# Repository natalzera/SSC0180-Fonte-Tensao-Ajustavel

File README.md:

# SSC0180-Fonte-Tensao-Ajustavel

## Objetivos
Montar/esquematizar uma fonte de tensão ajustável (corrente contínua)  entre 3V a 12V com capacidade de 100mA em 12V

## Componentes
Componente     | Quantidade | Preço Total(R$)
---            | ---        | ---
Transformador 15V 500mA | 1          | 31,60
Diodos 1N4007           | 4          | 0,40
Capacitor 470uF 25V     | 1          | 0,41
Resistor 470Ω        | 1          | 0,05
Diodo Zener 13V 0,5W    | 1          | 0,08
Potenciômetro 1KΩ        | 1          | 1,99
Resistor 390Ω        | 1          | 0,05
Transistor NPN 45V 500mA | 1          | 0,20
TOTAL | -- | 34.78

* Transformador.  
O transformador escolhido é o componente responsavel por abaixar a tensão da tomada (220 V) para uma tensão mais proxima da que que será trabalhada (12-3 V). O transformador em questão leva *110V ou 220V para 15V*.  
[link para compra](https://www.baudaeletronica.com.br/transformador-trafo-500ma-15v.html)
 
* Diodos.  
Os diodos são usados para formar a ponte retificadora/ ponte de diodos. Essa ponte é responsavel por proporcionar o maior aproveitamento da energia, abastecendo o circito com a corrente em ambos os ciclos da corrente alternada. O escolhido para o projeto é o *Diodo 1N4007*.  
[link para compra](https://www.baudaeletronica.com.br/diodo-1n4007.html)

* Capacitor.  
O capacitor é responsavel por carregar o sistema quando a tensão (vinda da ponde de diodos) está em declinio, estabilizando a tensão que vai para o restante do circuito e criando o "ripple". O capacitor escolhido é um de 470uF, para criar um riplle de até 10%
[link para compra](https://www.baudaeletronica.com.br/capacitor-eletrolitico-470uf-25v.html)

* Resistores.  
O circuito implementa 2 resistores.  
O primeiro, *de 470ohms*, é responsavel por limitar a corrente passando pelo diodo Zener e pelo potenciômetro. Esse valor foi calculado para causar uma queda de tensão de até 5V quando o ripple esta no minimo (~18V).  
O segundo, *de 390ohms*, limita a tensão minima para aproximadamente 3,7V, fazendo com que o potencial de saida do potenciômetro esteja sempre entre ~12,7 ~3,7V.  
[link para compra (470ohms)](https://www.baudaeletronica.com.br/resistor-470r-5-1-4w.html)  
[link para compra (390ohms)](https://www.baudaeletronica.com.br/resistor-390r-5-1-4w.html)  

* Diodo Zener  
O diodo Zener é usado como limitador de tensão no circuito. O diodo escolhido tem tensão de regulação de 13V, ou seja, ele limita a tensão na saida dele a 13V constantes. Ele sera usado para causar uma tensão de referência para o transistor. O escolhido foi o *Diodo Zener BZX55C*.  
[link para compra](https://www.baudaeletronica.com.br/diodo-zener-bzx55c-13v-0-5w.html)

* Potenciômetro  
O potenciômetro recebe a corrente em paralelo com o diodo Zener, e por tanto tem potencial fixo em aprimadamente 13V (ocorre uma pequena queda do potencial devido as conexões do componente no resto do circuito, mas essa é negligenciavel para nossas aplicações). Assim, ele contrala a tensão mínima (~3V) e máxima (~12V) que vai para o transistor de controle.  
[link para compra](https://www.baudaeletronica.com.br/potenciometro-linear-rotativo-de-1k-1000.html)

* Transistor  
Por fim, o transistor é responsavel por amplificar a corrente que passa pela carga. Utilizando a corrente que passa pela base como referência, ele amplifica essa em 100 vezes. No pior caso (12V) ele recebe 1mA na base, e emite 100mA pelo emissor. O transistor escolhido foi o *Transistor NPN BC337*.  
[link para compra](https://www.baudaeletronica.com.br/transistor-npn-bc337.html)

[Circuito simulado no falstad](https://www.falstad.com/circuit/circuitjs.html?ctz=CQAgjCAMB0l3BWcAOaAmA7MgnGB-kA2MAFgwTRBMJCRIGZaBTAWjDACgB3K5SENMmRUwNQcMgd6JEAC8mAOyYAnNvRYyIYaBlL0KyMNkFh4aVhigDY8W3cjJNjTrJFihbgWhmV5S1WDqJBzKnqL8JKJeMhEYkjwIJD4eJHwCHvG0SeCE-ImaxlDcnmjeVKnRRaH5lTXiVmBomZE04VmauUUALlTYYg7tAgP8ECyE0IYYaNgUJJB9eI1QOqTYkIn09KQYGITIlKb8ACZMAGYAhgCuADZdHADGIPoHnc-pEsvwZODYOrmQYHI9EIazQhF2nwBxVKmghTWEgJomRhQ2EKMRRR49CaAimqNxlEy2P48KeOMwhOhePqb3qyLxbTebUkRzJJIGFJyJJAJwuNzurM5aAQYjKpMovKutw4gupIrZ+IlZylAsq4oZnSVfOlADdwNlOaRYUjwCBXqYrPwYAgOAAVfXGxV4iKfPYkQnoLZ8AHIaTYDD0bCbSwsGCQQjg4w7QgikFrEhIGDYZMhXgklJpbxWp5rYpJNFlfPgCH0yjCsTUjIcQEyVIjCF1ypaeCQpAAJSYAGcAJadrrnBT3Jh5ioYxsYyQADwdOTRS0BEBkwltygHndOAHtlABbc5HLcAHU7eAAahxp1mBBb6Osr4wlyAAAobhRdJhHjtdbunbv3Pdb85zyeecKBzA58CoEBhAAYXOAAHc57m7LpD07E4jwAMW7W5VwAcyYbcgMDbAnkgSgGCQG86CgkAAC1FBUI9Ah1ID3SQPBKAQG9wAgh9n1fAArwduw3bcmC6ZQNyYgBrD8mFwm5-2UID8BI7wkAQTMKgfWDlFwwCsVA+oWneTEnlAtoTOZDgNyGM0YioeZhGJZYIG5HFGFtRROwAY6ktDziPFDdyOQDbJI7ErDmbBhDmVzTUoCKQC8hRfP8+CAGfOyPQL12wiTznwwjbJoQgHOitErXQAQapoTzvL8o8FFyv89MAoA)

------------------------------
### Projeto esquemático

------------------------------
### PCB

------------------------------
### Modelo da placa

## Calculos dos componentes
.
.

## Vídeo de explicação do circuito

## O grupo

André Molina Gregório

Adalton de Sena Almeida Filho

Lucas da Silva Claros

Gabriel Natal Coutinho

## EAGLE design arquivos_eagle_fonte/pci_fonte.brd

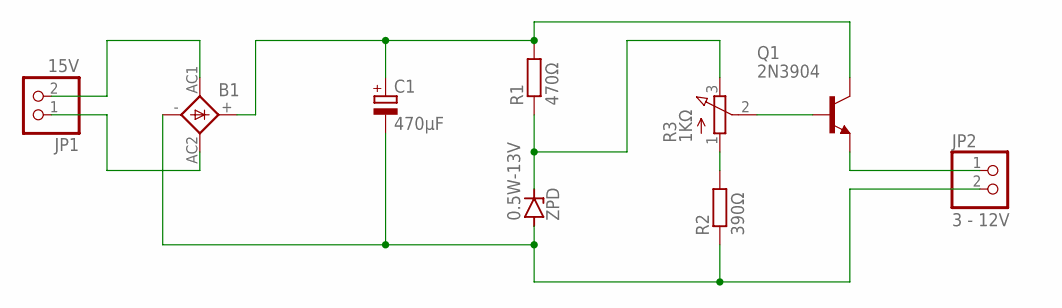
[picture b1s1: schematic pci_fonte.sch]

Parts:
0.5W-13V: ZPD; DO35Z10
B1: 1KAB
C1: 470µF; E3,5-10
JP1: 15V; 1X02
JP2: 3 - 12V; 1X02
Q1: 2N3904; TO92
R1: 470Ω; 0204/7
R2: 390Ω; 0204/7
R3: 1KΩ; 3RP/1610N

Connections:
unnamed: B1.AC1, JP1.2
unnamed: B1.AC2, JP1.1
unnamed: B1.+, C1.+, Q1.1 (C), R1.2
unnamed: Q1.2 (B), R3.2 (S)
unnamed: 0.5W-13V.C, R1.1, R3.3 (E)
unnamed: JP2.1, Q1.3 (E)
unnamed: R2.2, R3.1 (A)
unnamed: 0.5W-13V.A, B1.-, C1.-, JP2.2, R2.1

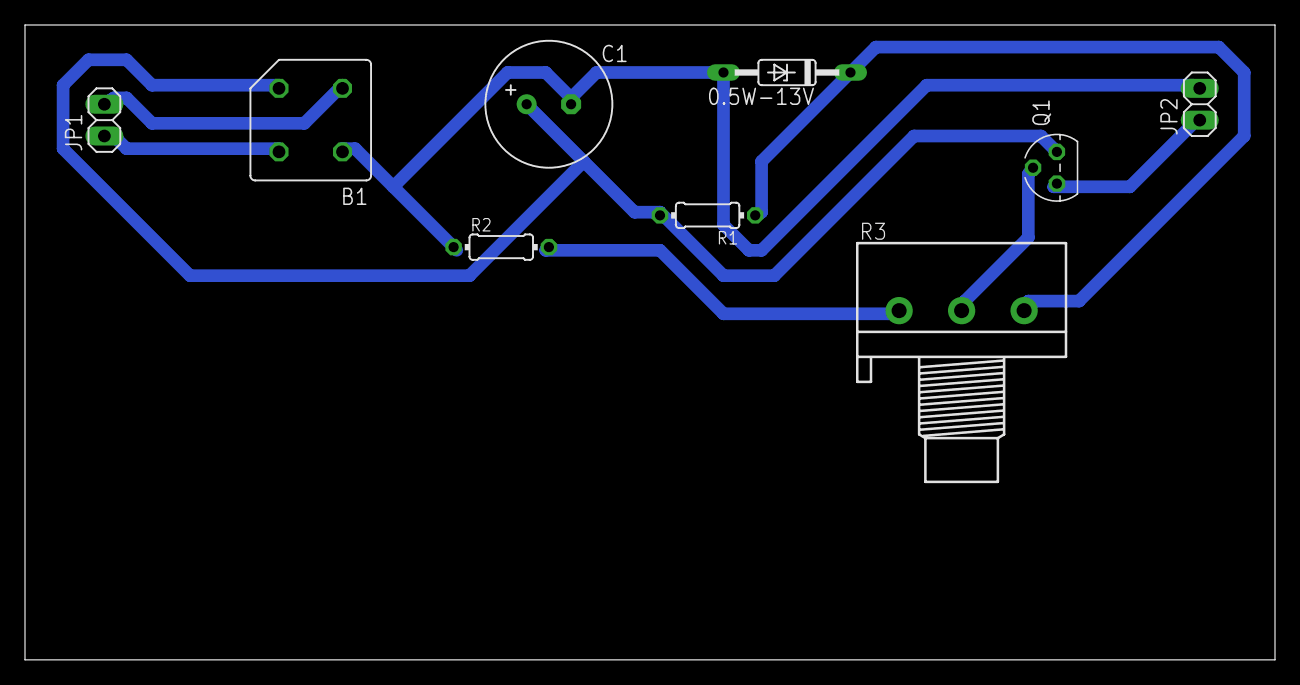
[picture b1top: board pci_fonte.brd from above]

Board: 2 copper layers, 100.0 x 50.8 mm, 9 parts (0 on the bottom side), 8 nets.

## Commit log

2021-07-21 Update README.md
    teste
2021-07-22 Mudei o resistor de 400 pra 390 só
